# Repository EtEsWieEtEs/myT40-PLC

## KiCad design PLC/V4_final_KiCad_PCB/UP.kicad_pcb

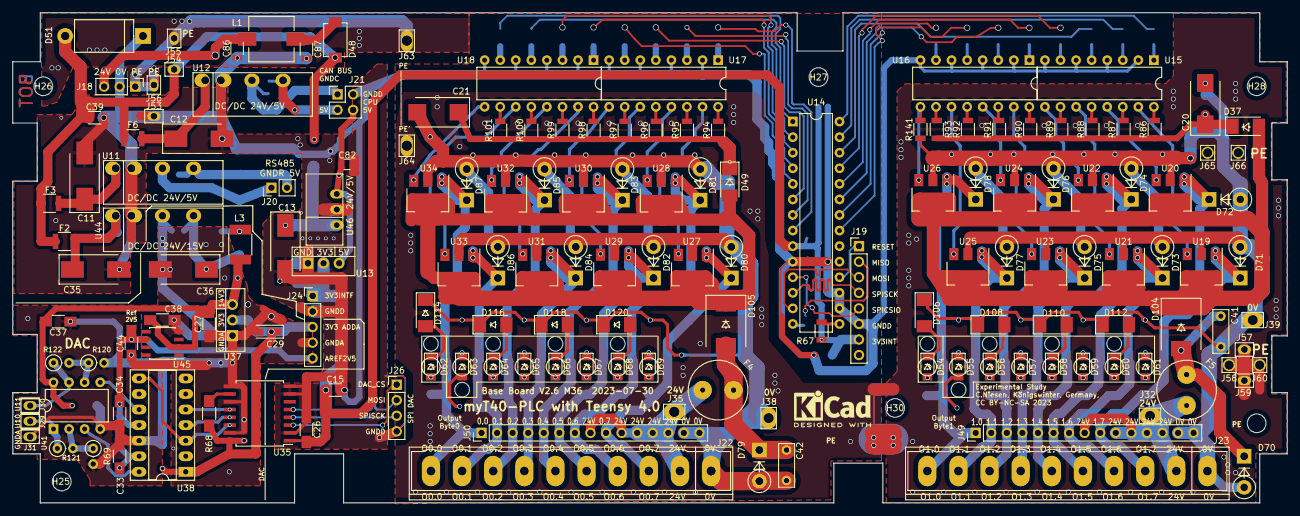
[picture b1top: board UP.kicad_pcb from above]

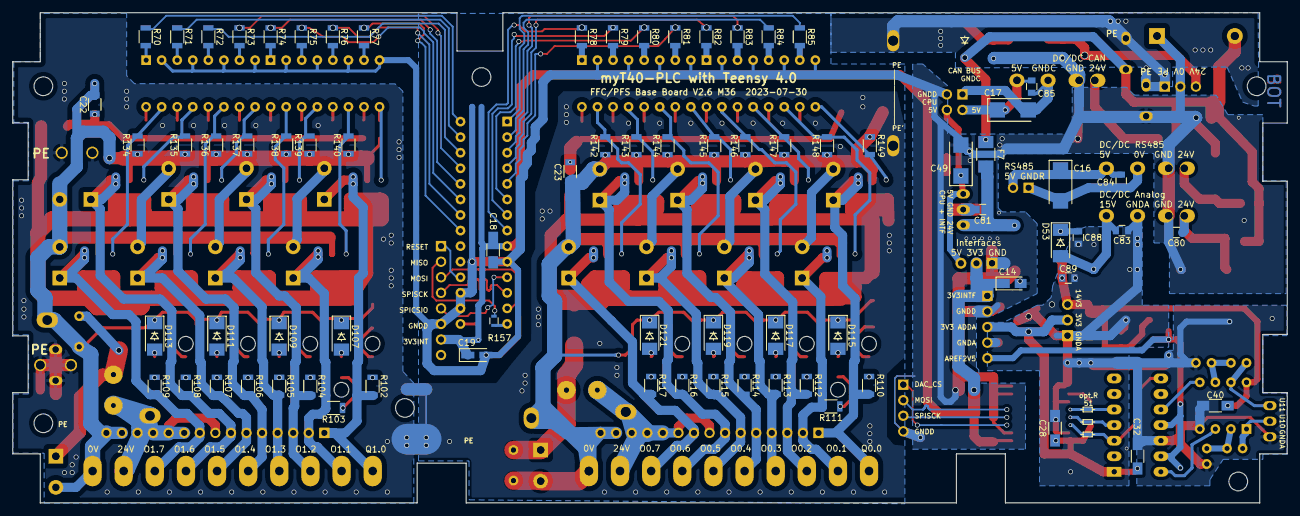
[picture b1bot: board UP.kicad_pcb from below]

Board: 2 copper layers, 208.0 x 80.0 mm, 245 parts (76 on the bottom side), 161 nets.

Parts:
A1: KiCad Symbol; KiCad-Logo2_6mm_SilkScreen
C11, C12, C13, C35: 10µ 50V; CP_Tantalum_Case-D_EIA-7343-31_Hand
C14: 22µ 6V3; CP_Tantalum_Case-A_EIA-3216-18_Reflow
C15, C39: 100n 50V; C_1206
C16, C17, C49: 22µ 10V; CP_Tantalum_Case-C_EIA-6032-28_Reflow
C18, C26, C27, C28, C32, C33, C34, C37, C38, C40, C44: 100n; C_1206_HandSoldering
C19: 2µ2 16V; CP_Tantalum_Case-A_EIA-3216-18_Wave
C20, C21: 2µ2 50V; CP_Tantalum_Case-D_EIA-7343-31_Wave
C22, C23, C86, C87: 100n; C_1206
C29: 10µ 10V; CP_Tantalum_Case-A_EIA-3216-18_Wave
C36: 22µ 25V; CP_Tantalum_Case-D_EIA-7343-31_Hand
C41, C42: 100n; C_Rect_L7.0mm_W2.5mm_P5.00mm
C80, C81, C82, C83, C84, C85, C88, C89: 100n 50V; C_0805
D37, D49, D106, D107, D108, D109, D110, D111, D112, D113, D114, D115, D116, D117, D118, D119, D120, D121: 1N4448W7F DII; Diode_DO213AB-MELF_SOD123
D48: MBRS 1100 SMD; DO-214AA_Schottky_man
D51: 1.5KE30CA; D_DO-201_P12.70mm_Horizontal
D53: 1N4007 SMD; Diode_DO213AB-MELF_SOD123
D54, D55, D56, D57, D58, D59, D60, D61, D62, D63, D64, D65, D66, D67, D68, D69: KPTD-3216; D_1206_4.5
D70, D71, D72, D73, D74, D75, D76, D77, D78, D79, D80, D81, D82, D83, D84, D85, D86, D87: P6KE36CA; D_DO-15_P5.08mm_Vertical_KathodeUp
D104, D105: SK86; D_SMC
F2, F3, F6: 50mA; R_1210
F4, F5: 6A3 T; Sockel_Kleinst-F
F7: 100mA; R_1210_HandSoldering
H25, H26, H27, H28, H29, H30: MountingHole; MountingHole_3mm
H31, H32: LED-Licht-Leiter_8x3mm_P5.08; MEN-LED-Lichtleiter_8x3mm_P5.08_5v8
J18: 01x03_Male; PinHeader_1x03_P2.54mm_Vertical
J19: 01x08_Male; PinHeader_1x08_P2.54mm_Vertical
J20: 01x02_Male; PinHeader_1x02_P2.54mm_Vertical
J21: 02x02_Male; PinHeader_2x02_P2.54mm_Vertical
J22, J23: opt. Connector; TerminalBlock_Phoenix_MSTBVA-2.5-10-5.08_1x10_P5.08mm_Horiz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
J24: 01x05_Male; PinHeader_1x05_P2.54mm_Vertical
J26: 01x04; PinHeader_1x04_P2.54mm_Vertical
J29, J30, J31, J53, J54, J55, J56, J57, J59: Lötauge; Lötauge-Junction
J32, J35, J38, J39: Lötauge; Lötauge-Junction-3.5x2.5-1.6
J49, J50: 01x15 Male zu OP; PinHeader_1x15_P2.54mm_Vertical
J58, J60, J65: Lötauge; Lötauge-Junction-2x2-1.4
J63, J64: Lötauge; Lötauge-Junction-3.5x2.0-1.6
J66: Flachstecker; Lötauge-Junction-2x2-1.4
L1: PIS2812-271M-04; L_7.3x7.3_H3.5_handsoldered
L3: L-1812AF 330µ 100mA; L_1812
R67: 10k; R_1206
R68: 10k; R_1206_HandSoldering
R69, R120: 1k 0,1%; R_Axial_DIN0207_L6.3mm_D2.5mm_P2.54mm_Vertical
R70, R71, R72, R73, R74, R75, R76, R77, R78, R79, R80, R81, R82, R83, R84, R85: 1650; R_1206
R86, R87, R88, R89, R90, R91, R92, R93, R94, R95, R96, R97, R98, R99, R100, R101, R102, R103, R104, R105, R106, R107, R108, R109, R110, R111, R112, R113, R114, R115, R116, R117, R134, R135, R136, R137, R138, R139, R140, R141, R142, R143, R144, R145, R146, R147, R148, R149: 6k8; R_1206
R121, R122: 3k0 0,1%; R_Axial_DIN0207_L6.3mm_D2.5mm_P2.54mm_Vertical
R157: 51; R_0603
U11, U12: 2S7WA_2405_S3RP; SIP-7_2S7WA
U13, U37: LT1086 3.3; TO-220-3_Vertical
U14: MCP23S17; DIP-28_W7.62mm
U15, U16, U17, U18: LTV-844; DIP-16_W7.62mm_cut
U19, U20, U21, U22, U23, U24, U25, U26, U27, U28, U29, U30, U31, U32, U33, U34: BSP-452; SOT-223
U35: ADuM1401xRW; SOIC-16W_7.5x10.3mm_Pitch1.27mm_handsoldered
U38: MCP4922; DIP-14_W7.62mm_Socket_LongPads
U41: LT 1078; DIP-8_W7.62mm
U44: 2S7WB_2415S3RP; SIP-7_2S7WA
U45: ADR03ARZ; SOIC-8_3.9x4.9mm_Pitch1.27mm
U46: LCN78_05-0.5; SIP-3-LC78

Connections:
+3V3: C14.1, C15.1, C18.2, C19.1, C26.2, J19.7, J24.1, R67.1, U13.2, U14.9, U35.1
/3V3_ADDA: C28.2, C29.1, C32.2, J24.3, R68.1, U35.16, U37.2, U38.1
/5V_CPU: C49.1, C82.1, J21.4, U13.3, U46.3
/12V_ADDA: C27.2, C37.2, C38.2, C40.2, C89.1, L3.1, U37.3, U41.8, U45.2
/24V_F4: C42.1, D79.1, D105.2, F4.2
/24V_F5: C41.1, D70.1, D104.2, F5.2
/24V_OPT_1: C20.1, C22.1, D37.1, R86.1, R87.1, R88.1, R89.1, R90.1, R91.1, R92.1, R93.1
/24V_OPT_2: C21.1, C23.1, D49.1, R94.1, R95.1, R96.1, R97.1, R98.1, R99.1, R100.1, R101.1
/24V_Out_0: D49.2, D105.1, U27.4, U28.4, U29.4, U30.4, U31.4, U32.4, U33.4, U34.4
/24V_Out_1: D37.2, D104.1, U19.4, U20.4, U21.4, U22.4, U23.4, U24.4, U25.4, U26.4
/AREF_2V5: C33.2, C34.2, C44.2, J24.5, U38.11, U38.13, U45.6
/DAC_A: U38.14, U41.3
/DAC_B: U38.10, U41.5
/DAC_OUT_A: J29.1, R121.1, U41.1
/DAC_OUT_B: J30.1, R122.1, U41.7
/GNDPWR_Out_0: C21.2, C23.2, C42.2, D79.2, D80.2, D81.2, D82.2, D83.2, D84.2, D85.2, D86.2, D87.2, D114.1, D115.1, D116.1, D117.1, D118.1, D119.1, D120.1, D121.1, J22.1, J38.1, J50.14, J50.15, R142.1, R143.1, R144.1, R145.1, R146.1, R147.1, R148.1, R149.1, U27.2, U28.2, U29.2, U30.2, U31.2, U32.2, U33.2, U34.2
/GNDPWR_Out_1: C20.2, C22.2, C41.2, D70.2, D71.2, D72.2, D73.2, D74.2, D75.2, D76.2, D77.2, D78.2, D106.1, D107.1, D108.1, D109.1, D110.1, D111.1, D112.1, D113.1, J23.1, J39.1, J49.14, J49.15, R134.1, R135.1, R136.1, R137.1, R138.1, R139.1, R140.1, R141.1, U19.2, U20.2, U21.2, U22.2, U23.2, U24.2, U25.2, U26.2
/GND_CAN_BUS: C17.2, C85.2, J21.1, U12.4
/GND_RS485_BUS: C16.2, C84.2, J20.1, U11.4
/MISO: J19.2, R157.1
/MOSI: J19.3, J26.2, U14.13, U35.5
/O_GPA0: R77.1, U14.21
/O_GPA1: R76.1, U14.22
/O_GPA2: R75.1, U14.23
/O_GPA3: R74.1, U14.24
/O_GPA4: R73.1, U14.25
/O_GPA5: R72.1, U14.26
/O_GPA6: R71.1, U14.27
/O_GPA7: R70.1, U14.28
/O_GPB0: R85.1, U14.1
/O_GPB1: R84.1, U14.2
/O_GPB2: R83.1, U14.3
/O_GPB3: R82.1, U14.4
/O_GPB4: R81.1, U14.5
/O_GPB5: R80.1, U14.6
/O_GPB6: R79.1, U14.7
/O_GPB7: R78.1, U14.8
/PE: J18.1, J55.1, J56.1, J57.1, J58.1, J59.1, J60.1, J63.1, J64.1, J65.1, J66.1
/SPISCK: J19.4, J26.3, U14.12, U35.4
/Ub_5V_RS485_BUS: C16.1, C84.1, J20.2, U11.6
/Ub_CAN_BUS: C17.1, C85.1, J21.3, U12.6
/~RESET: J19.1, U14.18
/~SPICS_DAC: J26.1, U35.3
/~SPICS_IO: J19.5, U14.11
GNDA: C27.1, C28.1, C29.2, C32.1, C33.1, C34.1, C36.2, C37.1, C38.1, C40.1, C44.1, C83.2, C88.2, C89.2, J24.4, J31.1, R69.2, R120.2, U35.9, U35.11, U35.15, U37.1, U38.12, U41.4, U44.4, U45.4
GNDD: C11.2, C12.2, C13.2, C14.2, C15.2, C18.1, C19.2, C26.1, C35.2, C39.2, C49.2, C80.2, C81.2, C82.2, C86.1, C87.1, D51.1, J18.2, J19.6, J21.2, J24.2, J26.4, J53.1, U11.2, U12.2, U13.1, U14.10, U14.16, U14.17, U15.2, U15.4, U15.6, U15.8, U16.2, U16.4, U16.6, U16.8, U17.2, U17.4, U17.6, U17.8, U18.2, U18.4, U18.6, U18.8, U35.2, U35.7, U35.8, U44.2, U46.2
unnamed: C11.1, F3.1, U11.1
unnamed: C12.1, F6.1, U12.1
unnamed: C13.1, C81.1, F7.1, U46.1
unnamed: C35.1, C80.1, F2.1, U44.1
unnamed: C36.1, C83.1, D53.2, U44.6
unnamed: C39.1, D48.1, D51.2, F2.2, F3.2, F6.2, F7.2, J54.1
unnamed: C86.2, J18.3, L1.2
unnamed: C87.2, D48.2, L1.1
unnamed: C88.1, D53.1, L3.2
unnamed: D54.2, R102.1
unnamed: D55.2, R103.1
unnamed: D56.2, R104.1
unnamed: D57.2, R105.1
unnamed: D58.2, R106.1
unnamed: D59.2, R107.1
unnamed: D60.2, R108.1
unnamed: D61.2, R109.1
unnamed: D62.2, R110.1
unnamed: D63.2, R111.1
unnamed: D64.2, R112.1
unnamed: D65.2, R113.1
unnamed: D66.2, R114.1
unnamed: D67.2, R115.1
unnamed: D68.2, R116.1
unnamed: D69.2, R117.1
unnamed: D71.1, J23.3, J49.9, R109.2, U19.1
unnamed: D72.1, J23.4, J49.7, R108.2, U20.1
unnamed: D73.1, J23.5, J49.6, R107.2, U21.1
unnamed: D74.1, J23.6, J49.5, R106.2, U22.1
unnamed: D75.1, J23.7, J49.4, R105.2, U23.1
unnamed: D76.1, J23.8, J49.3, R104.2, U24.1
unnamed: D77.1, J23.9, J49.2, R103.2, U25.1
unnamed: D78.1, J23.10, J49.1, R102.2, U26.1
unnamed: D80.1, J22.3, J50.9, R117.2, U27.1
unnamed: D81.1, J22.4, J50.7, R116.2, U28.1
unnamed: D82.1, J22.5, J50.6, R115.2, U29.1
unnamed: D83.1, J22.6, J50.5, R114.2, U30.1
unnamed: D84.1, J22.7, J50.4, R113.2, U31.1
unnamed: D85.1, J22.8, J50.3, R112.2, U32.1
unnamed: D86.1, J22.9, J50.2, R111.2, U33.1
unnamed: D87.1, J22.10, J50.1, R110.2, U34.1
unnamed: D54.1, D106.2
unnamed: D55.1, D107.2
unnamed: D56.1, D108.2
unnamed: D57.1, D109.2
unnamed: D58.1, D110.2
unnamed: D59.1, D111.2
unnamed: D60.1, D112.2
unnamed: D61.1, D113.2
unnamed: D62.1, D114.2
unnamed: D63.1, D115.2
unnamed: D64.1, D116.2
unnamed: D65.1, D117.2
unnamed: D66.1, D118.2
unnamed: D67.1, D119.2
unnamed: D68.1, D120.2
unnamed: D69.1, D121.2
unnamed: F4.1, J22.2, J35.1, J50.8, J50.10, J50.11, J50.12, J50.13
unnamed: F5.1, J23.2, J32.1, J49.8, J49.10, J49.11, J49.12, J49.13
unnamed: R67.2, U14.15
unnamed: R68.2, U35.10
unnamed: R70.2, U15.1
unnamed: R71.2, U15.3
unnamed: R72.2, U15.5
unnamed: R73.2, U15.7
unnamed: R74.2, U16.1
unnamed: R75.2, U16.3
unnamed: R76.2, U16.5
unnamed: R77.2, U16.7
unnamed: R78.2, U17.1
unnamed: R79.2, U17.3
unnamed: R80.2, U17.5
unnamed: R81.2, U17.7
unnamed: R82.2, U18.1
unnamed: R83.2, U18.3
unnamed: R84.2, U18.5
unnamed: R85.2, U18.7
unnamed: R86.2, U15.16
unnamed: R87.2, U15.14
unnamed: R88.2, U15.12
unnamed: R89.2, U15.10
unnamed: R90.2, U16.16
unnamed: R91.2, U16.14
unnamed: R92.2, U16.12
unnamed: R93.2, U16.10
unnamed: R94.2, U17.16
unnamed: R95.2, U17.14
unnamed: R96.2, U17.12
unnamed: R97.2, U17.10
unnamed: R98.2, U18.16
unnamed: R99.2, U18.14
unnamed: R100.2, U18.12
unnamed: R101.2, U18.10
unnamed: R120.1, R122.2, U41.6
unnamed: R69.1, R121.2, U41.2
unnamed: R134.2, U15.15, U19.3
unnamed: R135.2, U15.13, U20.3
unnamed: R136.2, U15.11, U21.3
unnamed: R137.2, U15.9, U22.3
unnamed: R138.2, U16.15, U23.3
unnamed: R139.2, U16.13, U24.3
unnamed: R140.2, U16.11, U25.3
unnamed: R141.2, U16.9, U26.3
unnamed: R142.2, U17.15, U27.3
unnamed: R143.2, U17.13, U28.3
unnamed: R144.2, U17.11, U29.3
unnamed: R145.2, U17.9, U30.3
unnamed: R146.2, U18.15, U31.3
unnamed: R147.2, U18.13, U32.3
unnamed: R148.2, U18.11, U33.3
unnamed: R149.2, U18.9, U34.3
unnamed: R157.2, U14.14
unnamed: U35.12, U38.5
unnamed: U35.13, U38.4
unnamed: U35.14, U38.3, U38.8

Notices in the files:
PLC/V4_final_KiCad_PCB/UP.kicad_pcb:
CC BY-NC-SA 2023
